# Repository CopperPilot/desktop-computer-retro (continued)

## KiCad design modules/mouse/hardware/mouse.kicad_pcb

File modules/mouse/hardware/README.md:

# Mouse PCBA Hardware Documentation

Generated from `rea/spec.yaml` by `rea-hardware` (JLCPCB 2-layer 1.6 mm stackup, design rules, 52.0 x 86.0 mm board outline at the origin, and M2 mounting holes), and completed for the single-button rectangular optical USB-C mouse. Every placed symbol carries a verified in-stock `LCSC` part number, matches the structured `rea/spec.yaml` BOM and power-tree definitions, and uses its matching `lcsc` footprint and 3D STEP model.

## Architecture & Blocks

1. **`usb_power` (USB-C Sink, 250 mA PPTC Fuse `F1`, Series P-MOSFET Reverse-Polarity Switch `Q2`, Transient ESD Clamp Reference `D1`, Critical Hot-Plug LC Damping, and 18V-VIN 3.3 V / 2.0 V CMOS LDO Regulation)**
   - **J1 (`TYPE-C-31-M-12`, LCSC `C165948`)**: 16-pin USB Type-C receptacle on the north edge (`+Y`, `rot_deg: 180`). Configured as a USB 2.0 Full-Speed sink with separate 5.1 kOhm 1% pull-down resistors **R1** (CC1) and **R2** (CC2) (`0603WAF5101T5E`, LCSC `C23186`) to `GND`.
   - **F1 (`BSMD0603-025-24V`, LCSC `C7543776`, `250 mA` $I_{\text{hold}}$ @ 25 degC / `190 mA >= 150 mA` @ 50 degC, `550 mA` $I_{\text{trip}}$, `24 V`, `40 A`, `500 mW`, `0603`, $R_{\min} = 0.50\ \Omega$, $R_{1\max} = 3.0\ \Omega$)**: Placed directly in series at `J1` VBUS entry (`USB_VBUS -> F1 -> VBUS_FUSED`), supporting both the 51.1 mA active / <= 80 mA continuous mouse load and the 150 mA `3V3_MOUSE` rail capability with thermal derating headroom (`190 mA @ 50 degC >= 150 mA`).
   - **Q2 (`AO3401A`, LCSC `C15127`, `SOT-23` P-Channel MOSFET), D6 (`BZT52C8V2S`, LCSC `C22375294`, `SOD-323` 8.2 V Zener), & R15 (`0603WAF1002T5E`, LCSC `C25804`, `10 kOhm`)**:
     - `Q2` sits in series between `VBUS_FUSED` (Drain, pin 3) and `VBUS_PROT` (Source, pin 2) with Gate (`VBUS_Q2_G`, pin 1) pulled down to `GND` via `R15` (`10 kOhm`) and clamped to Source (`VBUS_PROT`) by 8.2 V Zener diode `D6` (`BZT52C8V2S`, $V_Z = 7.7\text{--}8.7\text{ V}$, $I_R \le 700\text{ nA} @ 5\text{ V}$).
     - Under normal 5.0 V USB VBUS (`4.75-5.25 V`), `Q2` conducts in the third quadrant with $V_{GS} = -4.75\text{ V}$ to $-5.25\text{ V}$ and $R_{DS(\text{on})} \le 60\text{ m}\Omega$ (`3.1 mV` drop at `51.1 mA`, `9.0 mV` drop at `150 mA`).
     - During reverse polarity on `USB_VBUS` (down to `-24 V`), `Q2` is completely OFF ($V_{GS} = 0\text{ V}$ and Drain-to-Source body diode reverse-biased, $V_{DS,\max} = -30\text{ V}$), isolating `VBUS_PROT`, `D1`, and `5V_USB_MOUSE` / `U3` (`ME6209A33M3G`, `VIN_min = -0.3 V`) at `0.00 V`.
     - On high-voltage transients (up to `24 V`), `D6` clamps `Q2` $|V_{GS}| \le 8.7\text{ V} < 12.0\text{ V}$ (`AO3401A` absolute maximum $|V_{GS}|$).
   - **D1 (`USBLC6-2SC6`, LCSC `C2687116`) & C11 (`CC0603KRX7R9BB105`, LCSC `C559769`, `1 uF 50 V X7R 0603`)**:
     - `D1` sits at `(28.5, 9.8) mm` directly in-line on `USB_DP`/`USB_DM` between `J1` and `U1`. `USB_CC1` and `USB_CC2` are not connected to `USBLC6-2SC6`.
     - `D1` pin 5 (`VBUS` reference) and local high-frequency bypass capacitor `C11` (`1 uF 50 V X7R`) are connected to **`VBUS_PROT` downstream of both `F1` and `Q2`**, satisfying USB 2.0 Specification Section 7.2.4.1 (`C_RPB >= 1.0 uF`) and ST `USBLC6-2SC6` Application Note Figure 6. `D1` is used strictly for `8/20 us` IEC 61000-4-2 transient ESD clamping on `USB_DP`/`USB_DM` and `VBUS_PROT` — never as a continuous DC overvoltage or reverse-polarity crowbar.
   - **FB1 (`BLM18PG121SN1D`, LCSC `C14709`, `120 Ohm @ 100 MHz`, `2.0 A`, `50 mOhm` DCR) & R11 (`HP06W2F120KT5E`, LCSC `C414958`, `1.2 Ohm 1% 1206`, `500 mW` high-power)**:
     - Series overcurrent-protected, reverse-polarity-protected, and critically damped hot-plug input filter (`USB_VBUS -> F1 -> VBUS_FUSED -> Q2 -> VBUS_PROT -> FB1 -> VBUS_FB -> R11 -> 5V_USB_MOUSE`).
     - With `F1` resistance $R_{F1,\min} = 0.50\ \Omega$ ($R_{F1,\text{typ}} \approx 1.10\ \Omega$, $R_{1\max} = 3.00\ \Omega$), $R_{Q2,\text{typ}} = 0.04\ \Omega$ ($R_{Q2,\max} = 0.06\ \Omega$), $R_{FB1} = 0.05\ \Omega$, and $R_{R11} = 1.20\ \Omega$, total series damping resistance is $R_{\text{total,min}} = 1.79\ \Omega$ ($R_{\text{total,typ}} = 2.39\ \Omega$, $R_{\text{total,max}} = 4.31\ \Omega$), achieving hot-plug LC damping ratio $\zeta_{\min} = (1.79 / 2)\sqrt{1\ \mu\text{F} / 1\ \mu\text{H}} = 0.895 > 0.707$ ($\zeta_{\text{typ}} = 1.195 > 1.0$).
     - Worst-case post-reflow series voltage drop across `F1 + Q2 + FB1 + R11` ($R_{\max} = 4.31\ \Omega$) is `0.220 V` at `51.1 mA` (`0.122 V` typ), `0.345 V < 0.50 V` at `80 mA` (`0.191 V` typ), and `0.431 V < 0.50 V` at `100 mA` (`0.239 V` typ); at `150 mA`, `F1` drops `0.450 V < 0.50 V` (`0.165 V` typ) and total series drop is `0.359 V < 0.50 V` typ / `0.647 V` post-reflow max, keeping $V_{IN}(U3) = 4.75\text{ V} - 0.647\text{ V} = 4.103\text{ V} \ge 3.666\text{ V}$ (`+0.437 V` LDO dropout headroom).
     - **R11 (`HP06W2F120KT5E`, `1.2 Ohm`, `0.50 W` rated `1206`)** has a continuous current rating of $\sqrt{0.50\text{ W} / 1.2\ \Omega} = 645\text{ mA} > 550\text{ mA}$ (`F1` $I_{\text{trip}}$): it dissipates `3.13 mW` (`0.63%` of rating) at `51.1 mA` active mouse load, `0.30 W <= 0.50 W` (`60%` of rating) at `0.50 A`, and `0.363 W <= 0.50 W` (`72.6%` of rating) at `F1`'s `550 mA` trip threshold.
   - **U3 (`ME6209A33M3G`, LCSC `C83508`, `SOT-23-3L`)**: High-input-voltage (`18 V` max operating, `20 V` absolute maximum `VIN`), `250 mA`, `3.3 V +/- 2%` (`80 mV @ 40 mA` dropout, `3 uA` quiescent current) ceramic-stable CMOS low-dropout regulator stepping `5V_USB_MOUSE` down to `3V3_MOUSE`. Decoupled by **C1** (`CC0603KRX7R9BB105`, LCSC `C559769`, `1 uF 50 V X7R` input), **C2** (`CL10A475KA8NQNC`, LCSC `C69335`, `4.7 uF 25 V X5R` bulk reservoir on `3V3_MOUSE` at `U3`/`U4`), and local **C15** (`CC0603KRX7R9BB105`, LCSC `C559769`, `1 uF 50 V X7R` bulk bypass at `U1.5 VDDA` / `U1.1 VDD`) per ST AN4080 Section 3.1.1 / 3.1.2.
   - **U4 (`XC6206P202MR-G`, LCSC `C2891260`, `SOT-23-3L`)**: Ceramic-stable `2.00 V +/- 2%` (`1.960 V - 2.040 V`, `1 uA` quiescent current), `120 mA` CMOS LDO stepping `3V3_MOUSE` down to `2V0_SENSOR` (`2.0 V` nominal sensor core supply matching `PMW3901MB-TXQT` recommended `1.80 V min, 2.0 V typ, 2.10 V max` VDD window), decoupled by **C3** (`CL10A475KO8NNNC`, LCSC `C19666`, `4.7 uF 16 V X5R`) and **C10** (`CC0603KRX7R9BB104`, LCSC `C14663`, `100 nF 50 V X7R`).

2. **`mcu_hid` (USB 2.0 FS HID Microcontroller, 90-Ohm Coupled Differential USB Routing, Hardened Switch/DFU Protection, & SWD Recovery)**
   - **U1 (`STM32F042K6T6`, LCSC `C69216`)**: ARM Cortex-M0 48 MHz USB 2.0 Full-Speed MCU operating crystal-less via internal HSI48 + USB Clock Recovery System (CRS). Decoupled on `3V3_MOUSE` by **C2** (`4.7 uF 25 V X5R` VDD bulk reservoir), **C5, C6** (`100 nF 50 V X7R` per VDD pin), and the full ST AN4080 Section 3.1.2 `VDDA` (pin 5) analog/oscillator filter network **C15 (`1 uF 50 V X7R`) + C7 (`100 nF 50 V X7R`) + C13 (`10 nF 50 V X7R`, LCSC `C100042`)**.
   - **90-Ohm Coupled Differential Pair (`USB_DP` / `USB_DM`)**: Routed from `J1` through in-line ESD array `D1` to `U1` (`PA11`/`PA12`) on `F.Cu` over the unbroken `B.Cu` ground plane (`h = 1.51 mm` FR-4, `epsilon_r = 4.1`, `t = 0.035 mm`) using uniform coupled microstrip geometry **`w = 1.74 mm`, edge gap `s = 0.16 mm`**, achieving `Z_diff = 77.5 Ohm` (IPC-2141) / `101.9 Ohm` (edge-coupled analytical), both strictly inside `90 Ohm +/- 15%` (`76.5 - 103.5 Ohm`), with `1.03 mm` P/N length match (`<= 2.0 mm` limit) and `>= 92%` reference plane coverage.
   - **SW1 (`PTS526SM15SMTR2LFS`, LCSC `C2689538`)**: Top-mounted primary click tactile switch on `BTN_PRIMARY_SW`, pulled up to `3V3_MOUSE` by 10 kOhm **R4 (`0603WAF1002T5E`, LCSC `C25804`)**, protected by bidirectional SOD-323 ESD TVS diode **D5 (`PESD3V3L1BA`, LCSC `C2687129`)** to `GND`, and filtered through 1 kOhm series current-limiting resistor **R12 (`0603WAF1001T5E`, LCSC `C21190`)** and 100 nF hardware RC debounce capacitor **C12 (`CC0603KRX7R9BB104`, LCSC `C14663`)** (`tau = 1.1 ms`) into `BTN_PRIMARY` (`U1` pin 6 `PA0`).
   - **SW2 (`PTS526SM15SMTR2LFS`, LCSC `C2689538`)**: Bottom-mounted DFU boot tactile switch driving `BOOT0_SW` high to `3V3_MOUSE`. Protected by bidirectional SOD-323 ESD TVS diode **D4 (`PESD3V3L1BA`, LCSC `C2687129`)** to `GND`, 1 kOhm series resistor **R8 (`0603WAF1001T5E`, LCSC `C21190`)**, 10 kOhm pull-down **R3 (`0603WAF1002T5E`, LCSC `C25804`)**, and 100 nF hardware RC debounce capacitor **C14 (`CC0603KRX7R9BB104`, LCSC `C14663`)** on `MCU_BOOT0` (`U1` pin 31 `PB8/BOOT0`). `C14` charges in `0.10 ms` (`1 kOhm * 100 nF`) when `SW2` closes and holds `MCU_BOOT0` high with a `1.0 ms` time constant (`10 kOhm * 100 nF`) across contact-bounce openings so `BOOT0 = 1` is deterministically latched on the 4th `SYSCLK` rising edge after reset (with running firmware also debouncing `PB8` high for `>= 20 ms` before calling `NVIC_SystemReset()`).
   - **R5, R9, R10, R14 (`0603WAF1002T5E`, LCSC `C25804`, `10 kOhm`)**:
     - **R5 (`10 kOhm` pull-down to `GND` on `SENSOR_NRESET`)**: Holds `U2` pin 7 (`NRESET`, active-low reset) at `0 V` during power-on reset, brownout, and factory System Memory USB DFU bootloader operation (when `U1.PB1` is high-Z), ensuring `U2` stays in low-power reset (`< 20 uA`) until after both `3V3_MOUSE` and cascaded `2V0_SENSOR` (`U4`) have stabilized and application firmware actively drives `U1.PB1` high.
     - **R9, R10 (`10 kOhm` pull-ups to `3V3_MOUSE`)**: Deterministic pull-ups on AN2606 concurrent bootloader UART RX pins `PA10` (`USART1_RX`, pin 20, `R9`) and `PA15` (`USART2_RX`, pin 25, `R10`) so floating RX noise cannot lock out USB DFU enumeration.
     - **R14 (`10 kOhm` pull-up to `3V3_MOUSE`)**: Holds `SPI1_NCS` (`U2.19` / `U1.10`) inactive high during MCU reset and DFU bootloader operation.
   - **TP1–TP4 (`RH-5015`, LCSC `C5199798`)**: SMD recovery and debug test points exposing `SWDIO` (`PA13`), `SWCLK` (`PA14`), `MCU_NRST` (with 100 nF reset capacitor **C8**), and `GND`.

3. **`optical_sensor` (2D Optical Navigation Sensor, Thick-Lens Plano-Convex Aspheric Collimator (`f = 6.000 mm`, `FFD = 3.000 mm`, `+/-0.453 mm` Focus Window), Direct COB-28 Datum Stops & Switched Illumination LEDs)**
   - **U2 (`PMW3901MB-TXQT`, LCSC `C43496881`)**: Bottom-mounted 2D optical motion tracking sensor (`COB-28_L6.0-W6.0-P0.65-TL-EP`, verified as the sole in-stock optical navigation sensor in the JLCPCB/LCSC catalog) centered over the bottom optical aperture window at `(26.0, 45.5) mm`.
   - **Thick Plano-Convex Aspheric SLA Macro Collimator (`sensor_window`, `f = 6.000 mm` / `+166.7 D`, `FFD = 3.000 mm`) & Direct COB-28 Mechanical Datum Stops**:
     - Fabricated in optically clear polished SLA resin (`n = 1.51`, front desk-facing surface plano `R1 = infinity`, rear sensor-facing convex asphere `R2 = -3.060 mm`, center thickness `t_c = 4.530 mm`), yielding effective focal length `f = 6.000 mm`, front principal plane shift `delta_1 = 3.000 mm`, Front Focal Distance `FFD = 3.000 mm`, and working-distance tolerance window `d_desk in [2.581 mm, 3.486 mm]` (`+/-0.453 mm`, `0.905 mm` total window) with direct upper SLA mechanical datum stops against `U2`'s `COB-28` bottom face.
   - **D2, D3 (`KT-0603R`, LCSC `C2286`), R6, R7 (`0603WAF2200T5E`, LCSC `C22962`, `220 Ohm`), Q1 (`AO3400A`, LCSC `C20917`, `SOT-23`), & R13 (`0603WAF1002T5E`, LCSC `C25804`, `10 kOhm`)**:
     - Dual bottom-mounted (`B.Cu`) 630 nm AlGaInP red SMD LEDs flanking the optical aperture at `(27.5, 50.2) mm` and `(27.5, 52.5) mm`, supplied from `3V3_MOUSE` through individual 220 Ohm current-setting resistors (`I_F = (3.3 V - 1.9 V) / 220 Ohm = 6.36 mA` each, `12.73 mA` total) and switched on their cathode return path (`OPT_LED_K`) by N-channel MOSFET **Q1 (`AO3400A`)** + 10 kOhm pull-down **R13**.

## Component Voltage, Current, Capacitance, and Power Rating Checks

- **USB 2.0 Hot-Plug Capacitance (`1.0 uF <= C_RPB <= 10.0 uF`), Inrush Charge (`<= 50 uC`), & Capacitor Voltage Ratings (`>= 1.5x` Max Rail Voltage)**:
  - Direct 5 V VBUS port bypass capacitance (`VBUS_PROT + 5V_USB_MOUSE` ahead of LDO `U3`): **C11 (`1.0 uF 50 V X7R`) + C1 (`1.0 uF 50 V X7R`) = `2.0 uF`**, strictly within USB 2.0 Specification Section 7.2.4.1 (`1.0 uF <= C_RPB <= 10.0 uF`).
  - Total rail-weighted hot-plug charge across all rails (`10.0 uC` on 5.0 V from `C11 + C1 = 2.0 uF`; `20.16 uC` on 3.3 V from `C2 = 4.7 uF`, `C15 = 1.0 uF`, `C5-C7, C9 = 0.4 uF`, `C13 = 0.01 uF`; `9.60 uC` on 2.0 V from `C3 = 4.7 uF`, `C10 = 0.1 uF`; `8.46 uC` on 1.8 V from `C4 = 4.7 uF`) is **`48.22 uC <= 50.0 uC`** (`9.64 uF` equivalent at 5.0 V `<= 10.0 uF`), isolated by `F1 + Q2 + FB1 + R11` ($\zeta_{\min} = 0.895 > 0.707$, $\zeta_{\text{typ}} = 1.195 > 1.0$) and `U3`'s internal current limiting.
  - `VBUS_PROT` and `5V_USB_MOUSE` (5.0 V nominal, 5.25 V max USB VBUS): **C11, C1** (`CC0603KRX7R9BB105`, LCSC `C559769`, `1 uF 0603 X7R`) are rated at **50 V** (`10.0x` nominal 5.0 V, `9.5x` max 5.25 V).
  - `3V3_MOUSE` (3.3 V rail): **C2** (`CL10A475KA8NQNC`, LCSC `C69335`, `4.7 uF 0603 X5R`, **25 V** rated = `7.6x` rail voltage), **C15** (`CC0603KRX7R9BB105`, LCSC `C559769`, `1 uF 0603 X7R`, **50 V** rated = `15.1x` rail voltage), **C5, C6, C7, C8, C9, C12, C14** (`CC0603KRX7R9BB104`, LCSC `C14663`, `100 nF 0603 X7R`, **50 V** rated = `15.1x` rail voltage), and **C13** (`CC0603KRX7R9BB103`, LCSC `C100042`, `10 nF 0603 X7R`, **50 V** rated = `15.1x` rail voltage) all exceed the `1.5x` requirement.
  - `2V0_SENSOR` (2.0 V nominal sensor core rail) and `SENSOR_VREG` (1.8 V internal sensor rail): **C3, C4** (`CL10A475KO8NNNC`, LCSC `C19666`, `4.7 uF 0603 X5R`, **16 V** rated = `8.0x` rail voltage) and **C10** (`CC0603KRX7R9BB104`, `100 nF 0603 X7R`, **50 V** rated = `25.0x` rail voltage) exceed the `1.5x` requirement.
- **Connector, PTC Fuse, MOSFETs, Zener Clamp, Ferrite Bead & Damping Resistor Ratings**:
  - **J1 (`TYPE-C-31-M-12`, LCSC `C165948`)**: Dual VBUS contacts (`A4B9` and `B4A9`) and dual GND return contacts (`A1B12` and `B1A12` plus 4 PTH shield tabs) rated at **3.0 A** total.
  - **F1 (`BSMD0603-025-24V`, LCSC `C7543776`)**: Rated `I_hold = 250 mA` at 25 degC (`190 mA >= 150 mA` at 50 degC ambient, `3.72x` nominal `51.1 mA` load, `2.38x` continuous max `80 mA` load, `1.27x` full `150 mA` rail spec at 50 degC), `I_trip = 550 mA`, `V_max = 24 V` (`4.8x` nominal 5.0 V VBUS), `I_max = 40 A`, `P_d(typ) = 500 mW`, `R_min = 0.50 Ohm`, `R_1max = 3.0 Ohm`.
  - **Q2 (`AO3401A`, LCSC `C15127`, `SOT-23` P-MOSFET) & D6 (`BZT52C8V2S`, LCSC `C22375294`, `SOD-323` 8.2 V Zener)**: `Q2` is rated `V_DS(max) = -30 V` (`6.0x` nominal 5 V VBUS), `|V_GS(max)| = 12 V` (operating at `|V_GS| = 4.75-5.25 V = 43.8%` of abs max, and clamped by `D6` `BZT52C8V2S` + `R15` `10 kOhm` to `|V_GS| <= 8.7 V < 12 V` even up to `24 V` input), `R_DS(on) <= 60 mOhm @ V_GS = -4.5 V`, `I_D = -4.0 A` continuous vs. `51.1-150 mA` load (`<= 1.35 mW` conduction dissipation).
  - **Q1 (`AO3400A`, LCSC `C20917`, `SOT-23` N-MOSFET)**: Rated `V_DS(max) = 30 V` (`9.1x` the `3.3 V` LED rail), `|V_GS(max)| = 12 V` (`3.3 V` GPIO gate drive is `27.5%` of abs max `|V_GS|`), `R_DS(on) <= 48 mOhm @ V_GS = 2.5 V`, `I_D = 5.7 A` continuous vs. `12.73 mA` total LED sink current (`7.8 uW` dissipation).
  - **FB1 (`BLM18PG121SN1D`, LCSC `C14709`)**: Rated at **2.0 A** continuous (`50 mOhm` max DCR).
  - **R11 (`HP06W2F120KT5E`, LCSC `C414958`, `1.2 Ohm 1% 1206`, `500 mW`)**: Continuous current rating `sqrt(0.50 W / 1.2 Ohm) = 645 mA > 550 mA`; dissipates `3.13 mW` at `51.1 mA` active load, `0.30 W <= 0.50 W` at `0.5 A`, and `0.363 W <= 0.50 W` (`72.6%` of rating) at `F1`'s `550 mA` trip current.
- **Regulator Ratings**:
  - **U3 (`ME6209A33M3G`, LCSC `C83508`)**: Max operating input voltage **18.0 V** (abs max **20.0 V**, reverse `VIN` protected at `0.00 V >= -0.3 V` by `Q2`), rated output current `250 mA` vs. `51.1 mA` active / `150 mA` max `3V3_MOUSE` load (`>= +0.437 V` dropout headroom even at `150 mA` and post-reflow `R_1max = 3.0 Ohm`), unconditionally stable with low-ESR ceramic capacitors (`C1 = 1 uF`, `C2 = 4.7 uF`, `C15 = 1 uF`).
  - **U4 (`XC6206P202MR-G`, LCSC `C2891260`)**: `2.00 V +/- 2%` (`1.960 V - 2.040 V` at 25 degC), max input voltage `6.0 V` (operating at `3.3 V`), rated output current `120 mA` vs. `~15 mA` optical sensor core load, keeping `U2` `VDD` well inside `1.80 V - 2.10 V`.

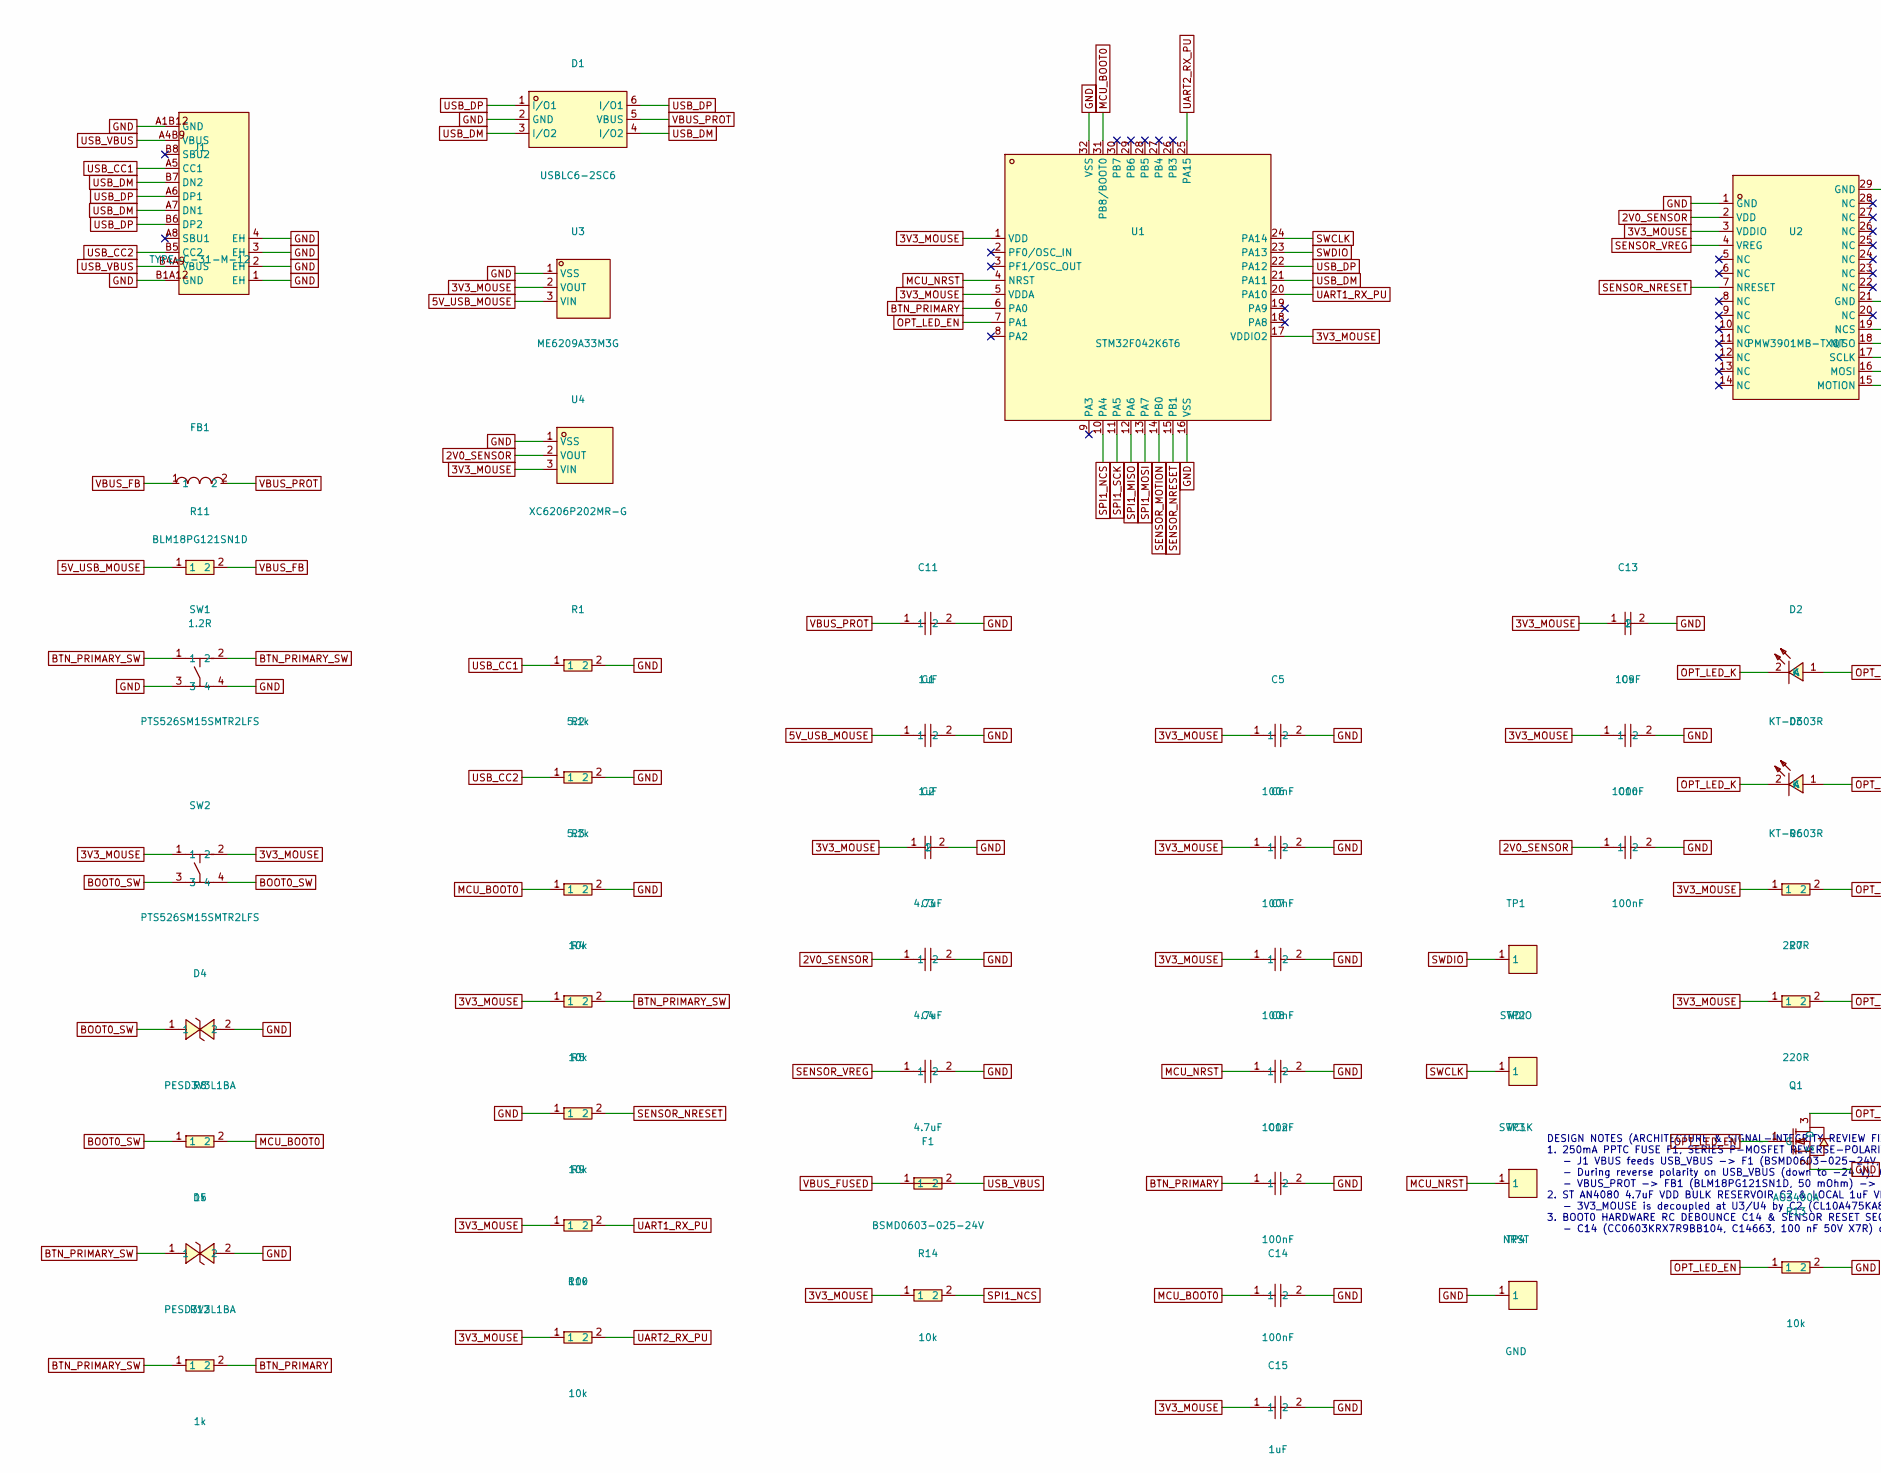
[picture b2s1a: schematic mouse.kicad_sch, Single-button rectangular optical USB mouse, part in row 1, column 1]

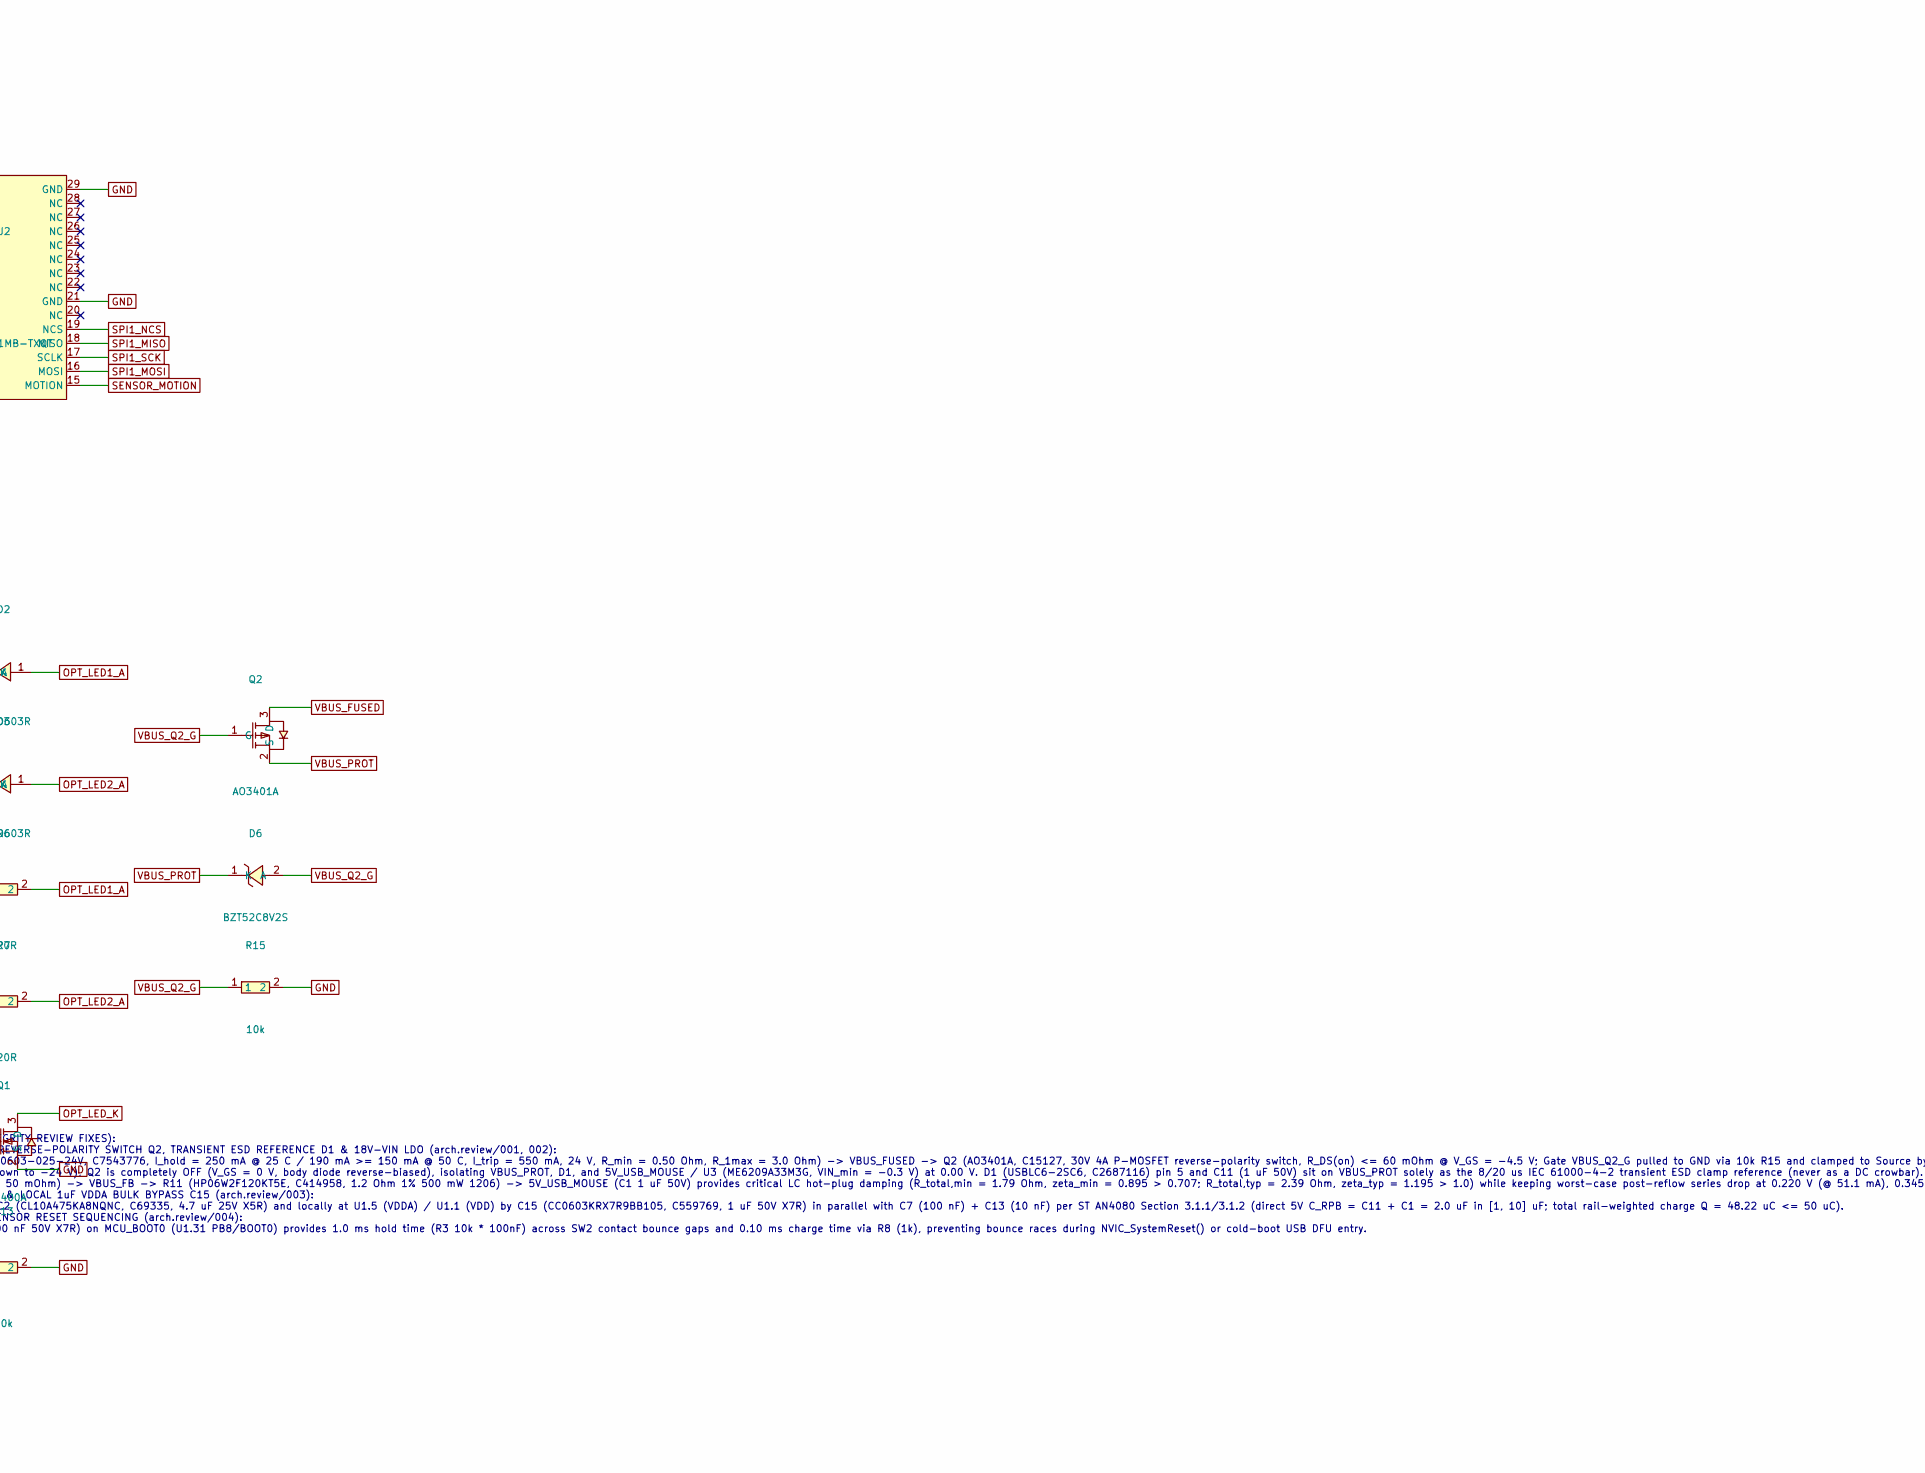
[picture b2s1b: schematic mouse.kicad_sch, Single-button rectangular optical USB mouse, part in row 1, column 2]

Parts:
C1, C11, C15: 1uF; C0603; MPN CC0603KRX7R9BB105; LCSC C559769
C2: 4.7uF; C0603; MPN CL10A475KA8NQNC; LCSC C69335
C3, C4: 4.7uF; C0603; MPN CL10A475KO8NNNC; LCSC C19666
C5, C6, C7, C8, C9, C10, C12, C14: 100nF; C0603; MPN CC0603KRX7R9BB104; LCSC C14663
C13: 10nF; C0603; MPN CC0603KRX7R9BB103; LCSC C100042
D1: USBLC6-2SC6; SOT-23-6_L2.9-W1.6-P0.95-LS2.8-BL; MPN USBLC6-2SC6; LCSC C2687116
D2, D3: KT-0603R; LED-SMD_L1.6-W0.8-R-RD; MPN KT-0603R; LCSC C2286
D4, D5: PESD3V3L1BA; SOD-323_L1.7-W1.3-LS2.6-BI; MPN PESD3V3L1BA; LCSC C2687129
D6: BZT52C8V2S; SOD-323_L1.7-W1.3-LS2.6-RD-1; MPN BZT52C8V2S; LCSC C22375294
F1: BSMD0603-025-24V; F0603; MPN BSMD0603-025-24V; LCSC C7543776
FB1: BLM18PG121SN1D; L0603; MPN BLM18PG121SN1D; LCSC C14709
J1: TYPE-C-31-M-12; USB-C_SMD-TYPE-C-31-M-12_1; MPN TYPE-C-31-M-12; LCSC C165948
Q1: AO3400A; SOT-23-3_L2.9-W1.3-P1.90-LS2.4-BR; MPN AO3400A; LCSC C20917
Q2: AO3401A; SOT-23_L2.9-W1.3-P1.90-LS2.4-BR; MPN AO3401A; LCSC C15127
R1, R2: 5.1k; R0603; MPN 0603WAF5101T5E; LCSC C23186
R3, R4, R5, R9, R10, R13, R14, R15: 10k; R0603; MPN 0603WAF1002T5E; LCSC C25804
R6, R7: 220R; R0603; MPN 0603WAF2200T5E; LCSC C22962
R8, R12: 1k; R0603; MPN 0603WAF1001T5E; LCSC C21190
R11: 1.2R; R1206; MPN HP06W2F120KT5E; LCSC C414958
SW1, SW2: PTS526SM15SMTR2LFS; SW-SMD_4P-L5.2-W5.2-P3.70-LS6.4; MPN PTS526SM15SMTR2LFS; LCSC C2689538
TP1: SWDIO; SMD_RH-5015; MPN RH-5015; LCSC C5199798
TP2: SWCLK; SMD_RH-5015; MPN RH-5015; LCSC C5199798
TP3: NRST; SMD_RH-5015; MPN RH-5015; LCSC C5199798
TP4: GND; SMD_RH-5015; MPN RH-5015; LCSC C5199798
U1: STM32F042K6T6; LQFP-32_L7.0-W7.0-P0.80-LS9.0-BL; MPN STM32F042K6T6; LCSC C69216
U2: PMW3901MB-TXQT; COB-28_L6.0-W6.0-P0.65-TL-EP; MPN PMW3901MB-TXQT; LCSC C43496881
U3: ME6209A33M3G; SOT-23-3_L2.9-W1.6-P1.90-LS2.8-BR; MPN ME6209A33M3G; LCSC C83508
U4: XC6206P202MR-G; SOT-23-3_L2.9-W1.6-P1.90-LS2.8-BR; MPN XC6206P202MR-G; LCSC C2891260

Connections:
2V0_SENSOR: C3.1, C10.1, U2.2 (VDD), U4.2 (VOUT)
3V3_MOUSE: C2.1, C5.1, C6.1, C7.1, C9.1, C13.1, C15.1, R4.1, R6.1, R7.1, R9.1, R10.1, R14.1, SW2.1, SW2.2, U1.1 (VDD), U1.5 (VDDA), U1.17 (VDDIO2), U2.3 (VDDIO), U3.2 (VOUT), U4.3 (VIN)
5V_USB_MOUSE: C1.1, R11.1, U3.3 (VIN)
BOOT0_SW: D4.1, R8.1, SW2.3, SW2.4
BTN_PRIMARY: C12.1, R12.2, U1.6 (PA0)
BTN_PRIMARY_SW: D5.1, R4.2, R12.1, SW1.1, SW1.2
GND: C1.2, C2.2, C3.2, C4.2, C5.2, C6.2, C7.2, C8.2, C9.2, C10.2, C11.2, C12.2, C13.2, C14.2, C15.2, D1.2 (GND), D4.2, D5.2, J1.1 (EH), J1.2 (EH), J1.3 (EH), J1.4 (EH), J1.A1B12 (GND), J1.B1A12 (GND), Q1.2 (S), R1.2, R2.2, R3.2, R5.1, R13.2, R15.2, SW1.3, SW1.4, TP4.1, U1.16 (VSS), U1.32 (VSS), U2.1 (GND), U2.21 (GND), U2.29 (GND), U3.1 (VSS), U4.1 (VSS)
MCU_BOOT0: C14.1, R3.1, R8.2, U1.31 (PB8/BOOT0)
MCU_NRST: C8.1, TP3.1, U1.4 (NRST)
OPT_LED1_A: D2.1 (A), R6.2
OPT_LED2_A: D3.1 (A), R7.2
OPT_LED_EN: Q1.1 (G), R13.1, U1.7 (PA1)
OPT_LED_K: D2.2 (K), D3.2 (K), Q1.3 (D)
SENSOR_MOTION: U1.14 (PB0), U2.15 (MOTION)
SENSOR_NRESET: R5.2, U1.15 (PB1), U2.7 (NRESET)
SENSOR_VREG: C4.1, U2.4 (VREG)
SPI1_MISO: U1.12 (PA6), U2.18 (MISO)
SPI1_MOSI: U1.13 (PA7), U2.16 (MOSI)
SPI1_NCS: R14.2, U1.10 (PA4), U2.19 (NCS)
SPI1_SCK: U1.11 (PA5), U2.17 (SCLK)
SWCLK: TP2.1, U1.24 (PA14)
SWDIO: TP1.1, U1.23 (PA13)
UART1_RX_PU: R9.2, U1.20 (PA10)
UART2_RX_PU: R10.2, U1.25 (PA15)
USB_CC1: J1.A5 (CC1), R1.1
USB_CC2: J1.B5 (CC2), R2.1
USB_DM: D1.3 (I/O2), D1.4 (I/O2), J1.A7 (DN1), J1.B7 (DN2), U1.21 (PA11)
USB_DP: D1.1 (I/O1), D1.6 (I/O1), J1.A6 (DP1), J1.B6 (DP2), U1.22 (PA12)
USB_VBUS: F1.2, J1.A4B9 (VBUS), J1.B4A9 (VBUS)
VBUS_FB: FB1.1, R11.2
VBUS_FUSED: F1.1, Q2.3 (D)
VBUS_PROT: C11.1, D1.5 (VBUS), D6.1 (K), FB1.2, Q2.2 (S)
VBUS_Q2_G: D6.2 (A), Q2.1 (G), R15.1

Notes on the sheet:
DESIGN NOTES (ARCHITECTURE & SIGNAL-INTEGRITY REVIEW FIXES): 1. 250mA PPTC FUSE F1, SERIES P-MOSFET REVERSE-POLARITY SWITCH Q2, TRANSIENT ESD REFERENCE D1 & 18V-VIN LDO (arch.review/001, 002): - J1 VBUS feeds USB_VBUS -> F1 (BSMD0603-025-24V, C7543776, I_hold = 250 mA @ 25 C / 190 mA >= 150 mA @ 50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

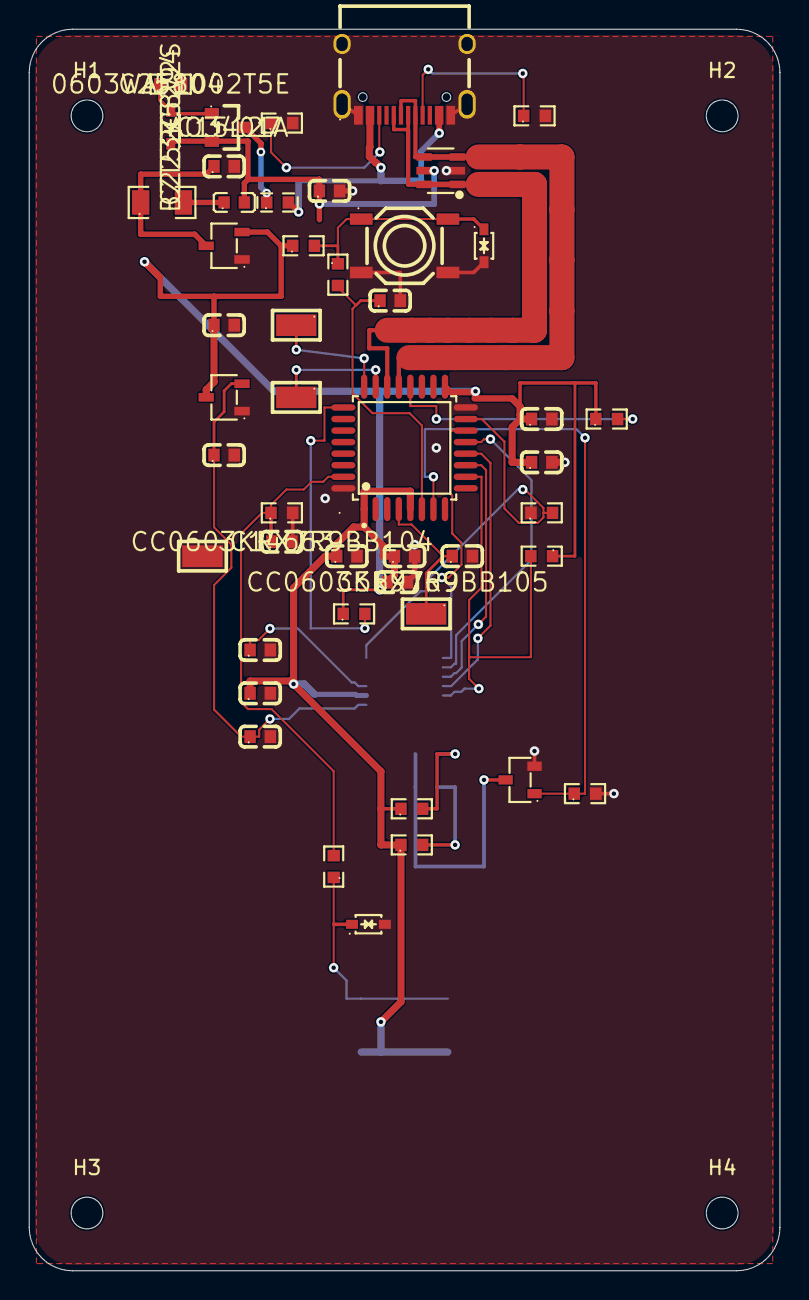
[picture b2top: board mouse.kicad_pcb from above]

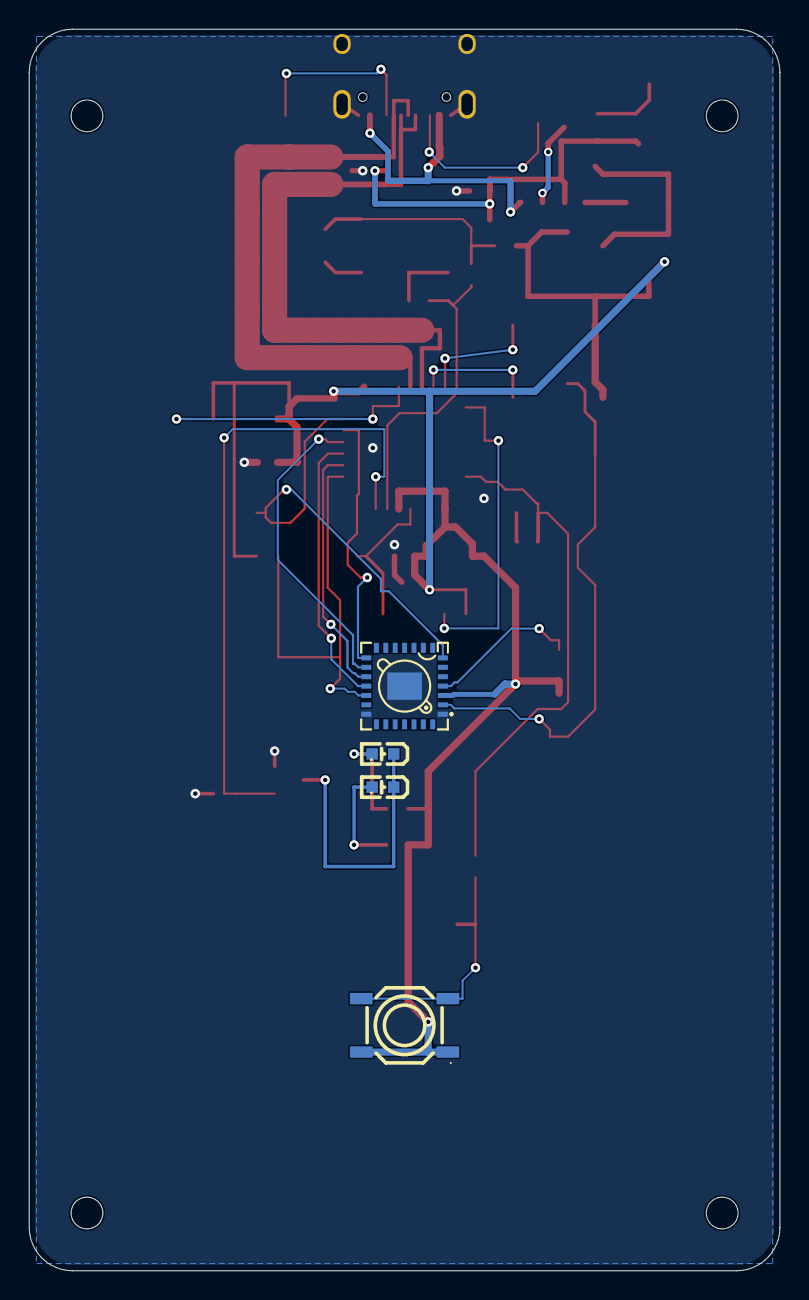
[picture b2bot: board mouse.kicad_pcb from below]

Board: 2 copper layers, 52.0 x 86.0 mm, 55 parts (4 on the bottom side), 33 nets.

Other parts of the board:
H1, H2, H3, H4: MountingHole_2.2mm_M2

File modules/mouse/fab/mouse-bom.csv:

Comment,Designator,Footprint,LCSC Part #
1uF,"C1,C11,C15",C0603,C559769
100nF,"C5,C6,C7,C8,C9,C10,C12,C14",C0603,C14663
10nF,C13,C0603,C100042
4.7uF,C2,C0603,C69335
4.7uF,"C3,C4",C0603,C19666
USBLC6-2SC6,D1,SOT-23-6_L2.9-W1.6-P0.95-LS2.8-BL,C2687116
KT-0603R,"D2,D3",LED-SMD_L1.6-W0.8-R-RD,C2286
PESD3V3L1BA,"D4,D5",SOD-323_L1.7-W1.3-LS2.6-BI,C2687129
BZT52C8V2S,D6,SOD-323_L1.7-W1.3-LS2.6-RD-1,C22375294
BSMD0603-025-24V,F1,F0603,C7543776
BLM18PG121SN1D,FB1,L0603,C14709
TYPE-C-31-M-12,J1,USB-C_SMD-TYPE-C-31-M-12_1,C165948
AO3400A,Q1,SOT-23-3_L2.9-W1.3-P1.90-LS2.4-BR,C20917
AO3401A,Q2,SOT-23_L2.9-W1.3-P1.90-LS2.4-BR,C15127
5.1k,"R1,R2",R0603,C23186
10k,"R3,R4,R5,R9,R10,R13,R14,R15",R0603,C25804
1.2R,R11,R1206,C414958
1k,"R8,R12",R0603,C21190
220R,"R6,R7",R0603,C22962
PTS526SM15SMTR2LFS,"SW1,SW2",SW-SMD_4P-L5.2-W5.2-P3.70-LS6.4,C2689538
STM32F042K6T6,U1,LQFP-32_L7.0-W7.0-P0.80-LS9.0-BL,C69216
PMW3901MB-TXQT,U2,COB-28_L6.0-W6.0-P0.65-TL-EP,C43496881
ME6209A33M3G,U3,SOT-23-3_L2.9-W1.6-P1.90-LS2.8-BR,C83508
XC6206P202MR-G,U4,SOT-23-3_L2.9-W1.6-P1.90-LS2.8-BR,C2891260
